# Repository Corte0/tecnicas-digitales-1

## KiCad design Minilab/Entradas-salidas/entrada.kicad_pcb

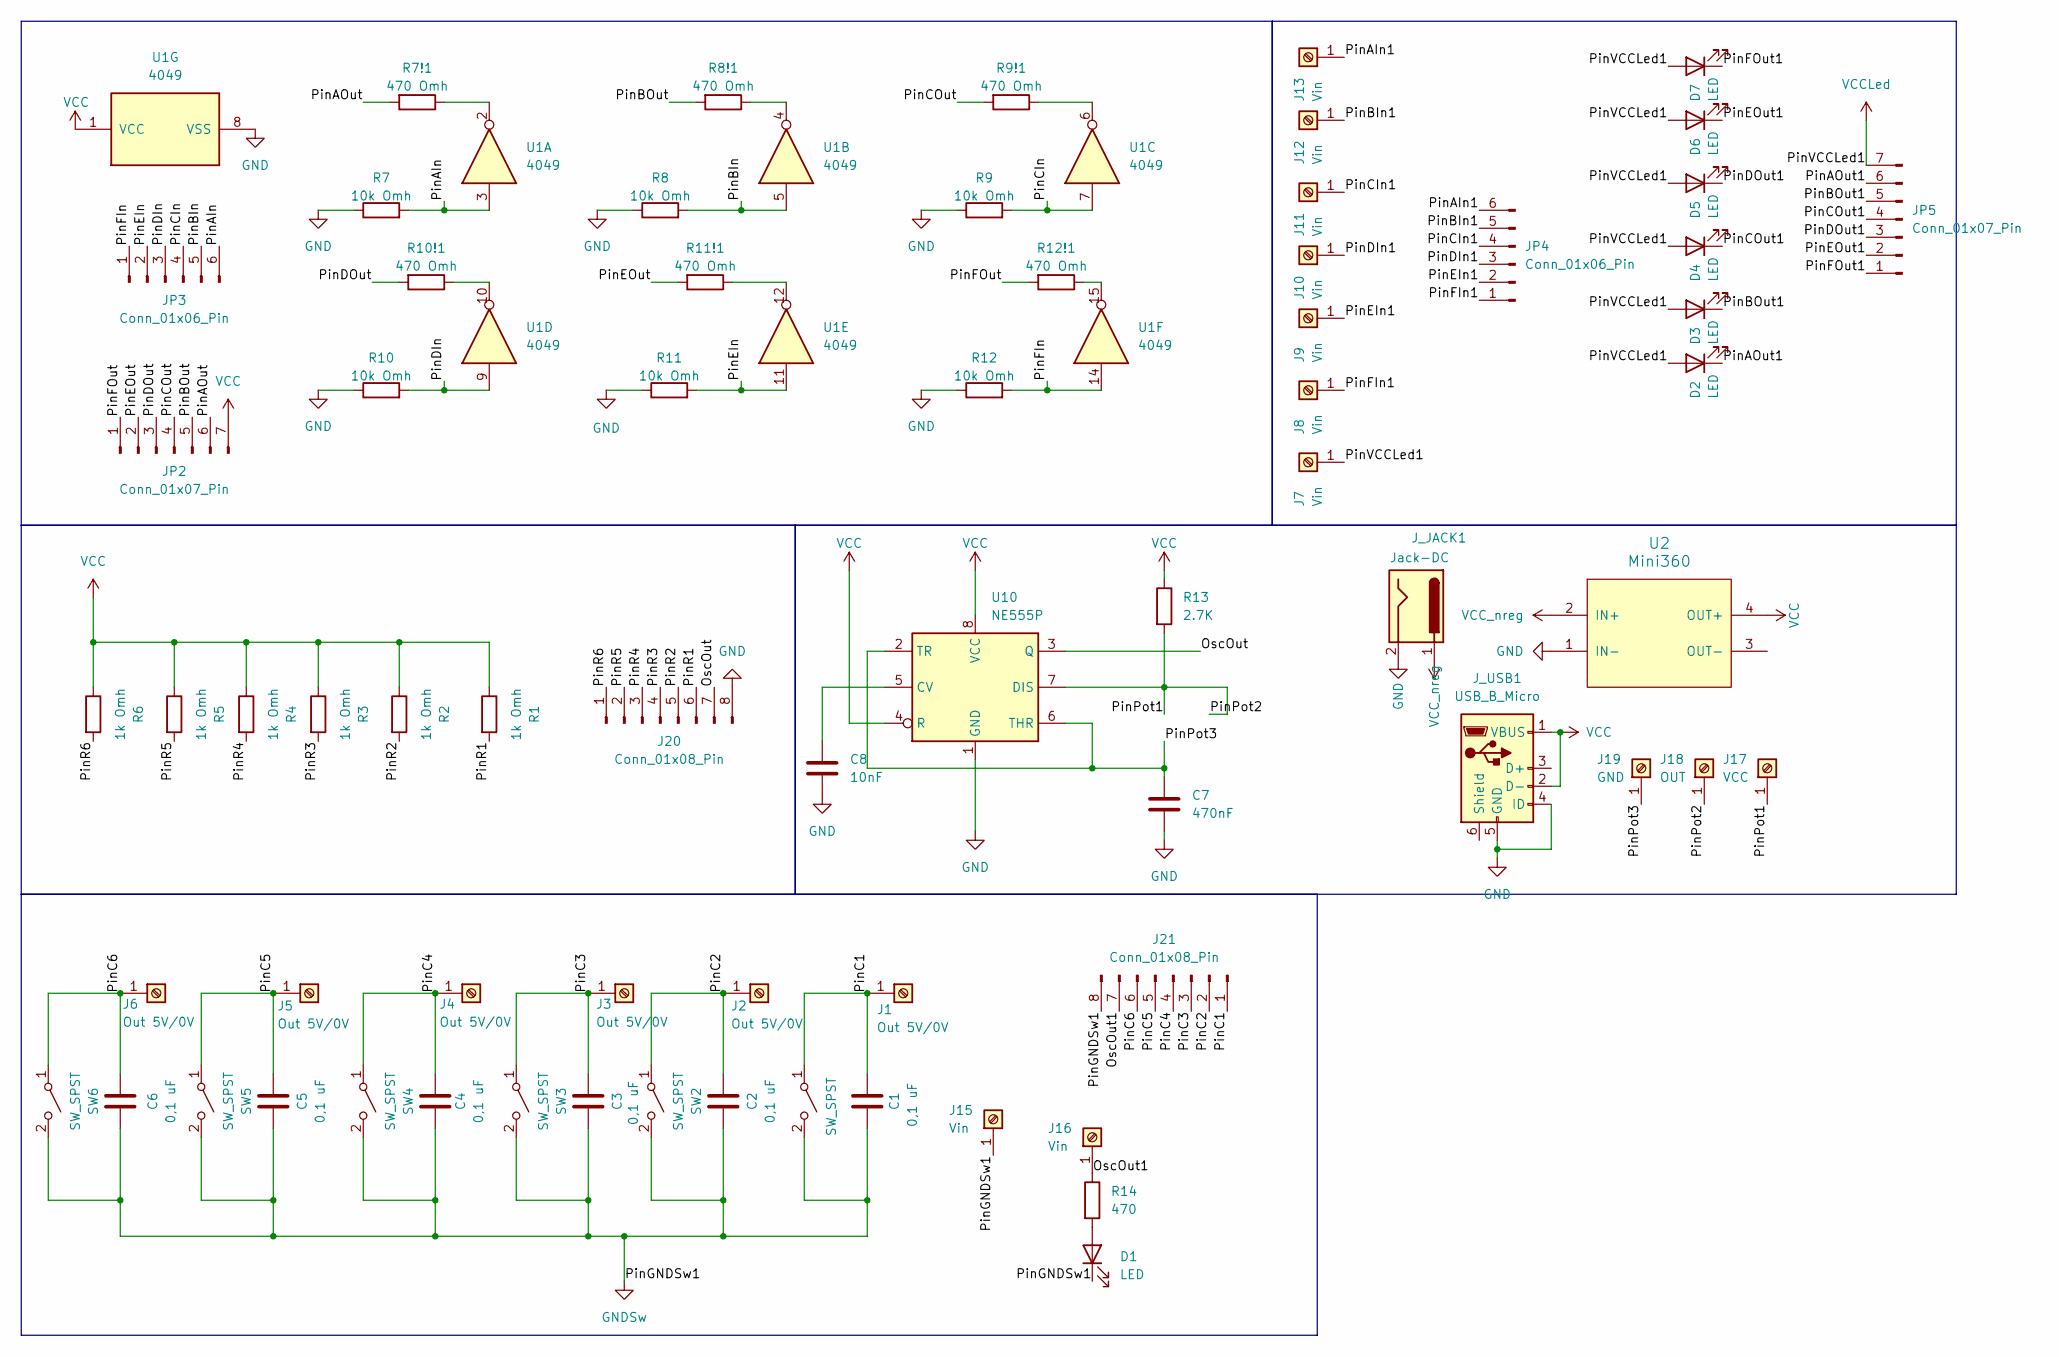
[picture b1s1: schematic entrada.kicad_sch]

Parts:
C1, C2, C3, C4, C5, C6: 0,1 uF; C_Disc_D5.0mm_W2.5mm_P2.50mm
C7: 470nF; C_Disc_D5.0mm_W2.5mm_P2.50mm
C8: 10nF; C_Disc_D5.0mm_W2.5mm_P2.50mm
D1, D2, D3, D4, D5, D6, D7: LED; LED_D5.0mm
J1, J2, J3, J4, J5, J6: Out 5V/0V; PinSocket_1x01_P2.00mm_Vertical
J7, J8, J9, J10, J11, J12, J13, J15, J16: Vin; PinSocket_1x01_P2.00mm_Vertical
J17: VCC; PinSocket_1x01_P2.00mm_Vertical
J18: OUT; PinSocket_1x01_P2.00mm_Vertical
J19: GND; PinSocket_1x01_P2.00mm_Vertical
J20: Conn_01x08_Pin; PinHeader_1x08_P2.54mm_Vertical
J21: Conn_01x08_Pin; PinSocket_1x08_P2.54mm_Vertical
JP2: Conn_01x07_Pin; PinHeader_1x07_P2.54mm_Vertical
JP3: Conn_01x06_Pin; PinHeader_1x06_P2.54mm_Vertical
JP4: Conn_01x06_Pin; PinSocket_1x06_P2.54mm_Vertical
JP5: Conn_01x07_Pin; PinSocket_1x07_P2.54mm_Vertical
J_JACK1: Jack-DC; BarrelJack_Horizontal
J_USB1: USB_B_Micro; usb
R1, R2, R3, R4, R5, R6: 1k Omh; R_Axial_DIN0204_L3.6mm_D1.6mm_P7.62mm_Horizontal
R7, R8, R9, R10, R11, R12: 10k Omh; R_Axial_DIN0204_L3.6mm_D1.6mm_P7.62mm_Horizontal
R7!1, R8!1, R9!1, R10!1, R11!1, R12!1: 470 Omh; R_Axial_DIN0204_L3.6mm_D1.6mm_P7.62mm_Horizontal
R13: 2.7K; R_Axial_DIN0204_L3.6mm_D1.6mm_P7.62mm_Horizontal
R14: 470; R_Axial_DIN0204_L3.6mm_D1.6mm_P7.62mm_Horizontal
SW1, SW2, SW3, SW4, SW5, SW6: SW_SPST; SW_Slide_SPDT_Straight_CK_OS102011MS2Q
U1: 4049; CERDIP-16_W7.62mm_SideBrazed
U2: Mini360; Mini360_step-down
U10: NE555P; DIP-8_W7.62mm

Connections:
/OscOut: J20.7, U10.3 (Q)
/OscOut1: J16.1, J21.7, R14.1
/PinAIn: JP3.6, R7.2, U1.3
/PinAIn1: J13.1, JP4.6
/PinAOut: JP2.6, R7!1.2
/PinAOut1: D2.1 (K), JP5.6
/PinBIn: JP3.5, R8.2, U1.5
/PinBIn1: J12.1, JP4.5
/PinBOut: JP2.5, R8!1.2
/PinBOut1: D3.1 (K), JP5.5
/PinC1: C1.2, J1.1, J21.1, SW1.1 (A)
/PinC2: C2.2, J2.1, J21.2, SW2.1 (A)
/PinC3: C3.2, J3.1, J21.3, SW3.1 (A)
/PinC4: C4.2, J4.1, J21.4, SW4.1 (A)
/PinC5: C5.2, J5.1, J21.5, SW5.1 (A)
/PinC6: C6.2, J6.1, J21.6, SW6.1 (A)
/PinCIn: JP3.4, R9.2, U1.7
/PinCIn1: J11.1, JP4.4
/PinCOut: JP2.4, R9!1.2
/PinCOut1: D4.1 (K), JP5.4
/PinDIn: JP3.3, R10.2, U1.9
/PinDIn1: J10.1, JP4.3
/PinDOut: JP2.3, R10!1.2
/PinDOut1: D5.1 (K), JP5.3
/PinEIn: JP3.2, R11.2, U1.11
/PinEIn1: J9.1, JP4.2
/PinEOut: JP2.2, R11!1.2
/PinEOut1: D6.1 (K), JP5.2
/PinFIn: JP3.1, R12.2, U1.14
/PinFIn1: J8.1, JP4.1
/PinFOut: JP2.1, R12!1.2
/PinFOut1: D7.1 (K), JP5.1
/PinPot1: J17.1, J18.1, R13.2, U10.7 (DIS)
/PinPot3: C7.1, J19.1, U10.2 (TR), U10.6 (THR)
/PinR1: J20.6, R1.2
/PinR2: J20.5, R2.2
/PinR3: J20.4, R3.2
/PinR4: J20.3, R4.2
/PinR5: J20.2, R5.2
/PinR6: J20.1, R6.2
GND: C7.2, C8.2, J20.8, J_JACK1.2, J_USB1.4 (ID), J_USB1.5 (GND), R7.1, R8.1, R9.1, R10.1, R11.1, R12.1, U1.8 (VSS), U2.1 (IN-), U10.1 (GND)
GNDSw: C1.1, C2.1, C3.1, C4.1, C5.1, C6.1, D1.1 (K), J15.1, J21.8, SW1.2 (B), SW2.2 (B), SW3.2 (B), SW4.2 (B), SW5.2 (B), SW6.2 (B)
unnamed: D1.2 (A), R14.2
unnamed: R7!1.1, U1.2
unnamed: R8!1.1, U1.4
unnamed: R9!1.1, U1.6
unnamed: R10!1.1, U1.10
unnamed: R11!1.1, U1.12
unnamed: R12!1.1, U1.15
unnamed: C8.1, U10.5 (CV)
VCC: JP2.7, J_USB1.1 (VBUS), J_USB1.2 (D-), R1.1, R2.1, R3.1, R4.1, R5.1, R6.1, R13.1, U1.1 (VCC), U2.4 (OUT+), U10.4 (R), U10.8 (VCC)
VCCLed: D2.2 (A), D3.2 (A), D4.2 (A), D5.2 (A), D6.2 (A), D7.2 (A), J7.1, JP5.7
VCC_nreg: J_JACK1.1, U2.2 (IN+)

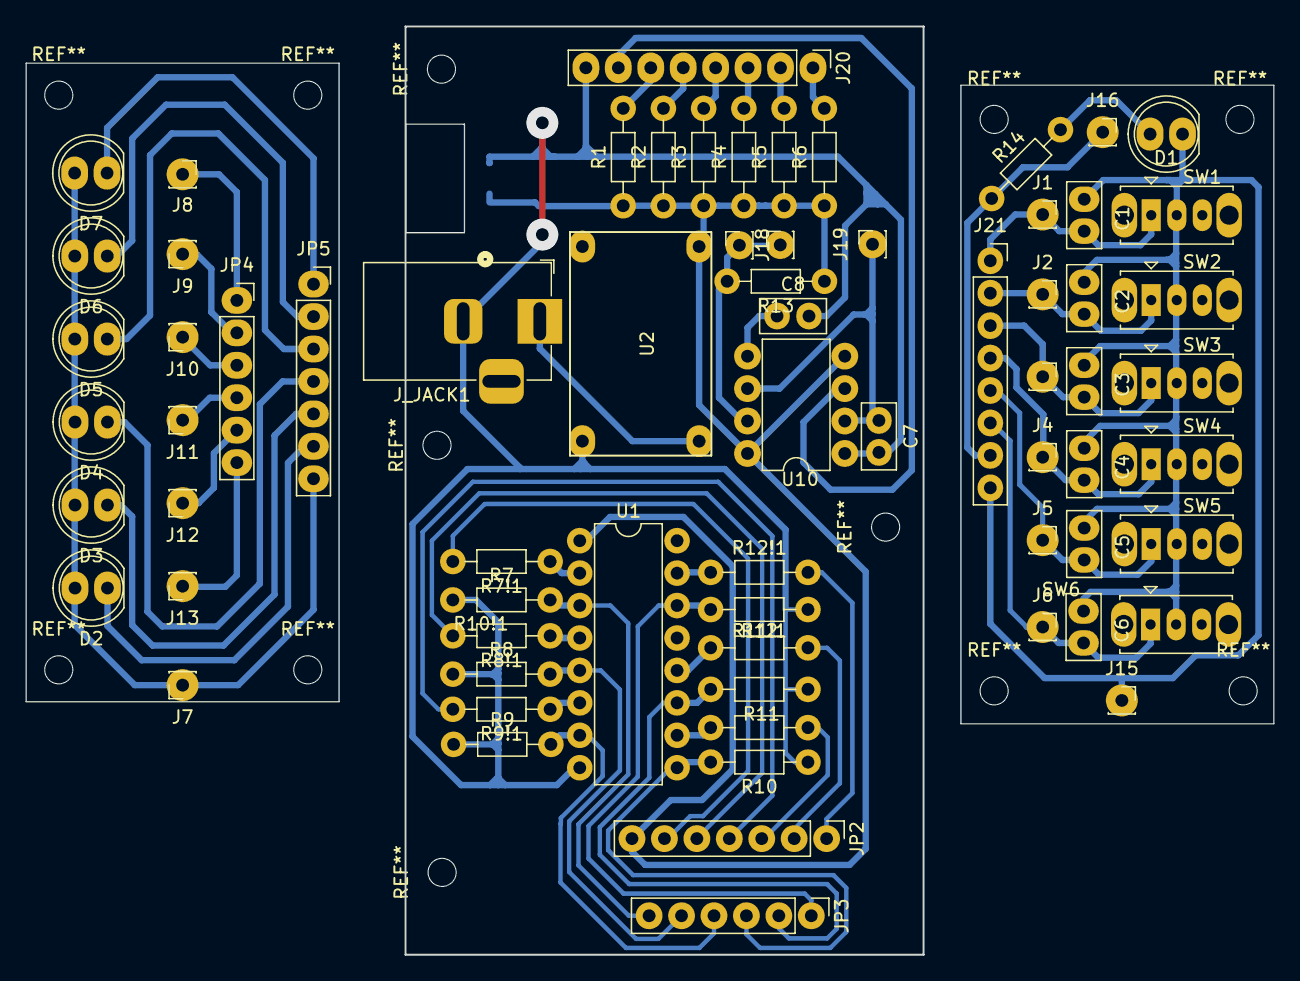
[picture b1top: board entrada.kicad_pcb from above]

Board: 2 copper layers, 97.7 x 72.7 mm, 70 parts (1 on the bottom side), 53 nets.

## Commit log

2025-03-25 sube documentos
2025-04-07 Entrada-salida minilab
2025-04-07 Muevo archivos a carpeta
2025-04-08 cambio de CI de entradas y oscilador
2025-04-10 Continuacion .sch
    Continuacion .sch
2025-04-10 Cotas .pcb
    Cotas .pcb
2025-04-10 Ordeno un poco
2025-04-10 casi terminado .sch
2025-04-26 avance pcb y agregado mini360
2025-04-27 reordenado de led y pines placa sec
2025-04-28 avance placa sec con switches
2025-05-12 FIN PLACA 2
    FIN PLACA 2
2025-05-12 lindo avance placa principal
2025-05-20 avance piolita en placa principal
2025-05-20 revision final
2025-05-21 hecho plano de masa y tornillos
2025-05-23 cambio oscilador
2025-05-23 listo para planchar
2025-06-08 tp1: comienzo
2025-06-08 Agrega implementación con compuertas del punto 1
2025-06-08 Corrige circuito
    En la primer and de Y2, iba !C no C
2025-06-08 Agrega circuito 2do pto
2025-06-08 casi terminado ej1
2025-06-09 punto 2.2
2025-06-10 arreglo la cagada que hizo pedro. No compilaba xdx
2025-06-10 conclusiones y comparador binario
2025-06-13 sube modelos 3d
2025-06-13 Agrega imagen del circuito 1 en el minilab
2025-09-09 agrega verilog tp2
2026-04-13 add initial report on FPGA and CPLD, including definitions and comparisons
